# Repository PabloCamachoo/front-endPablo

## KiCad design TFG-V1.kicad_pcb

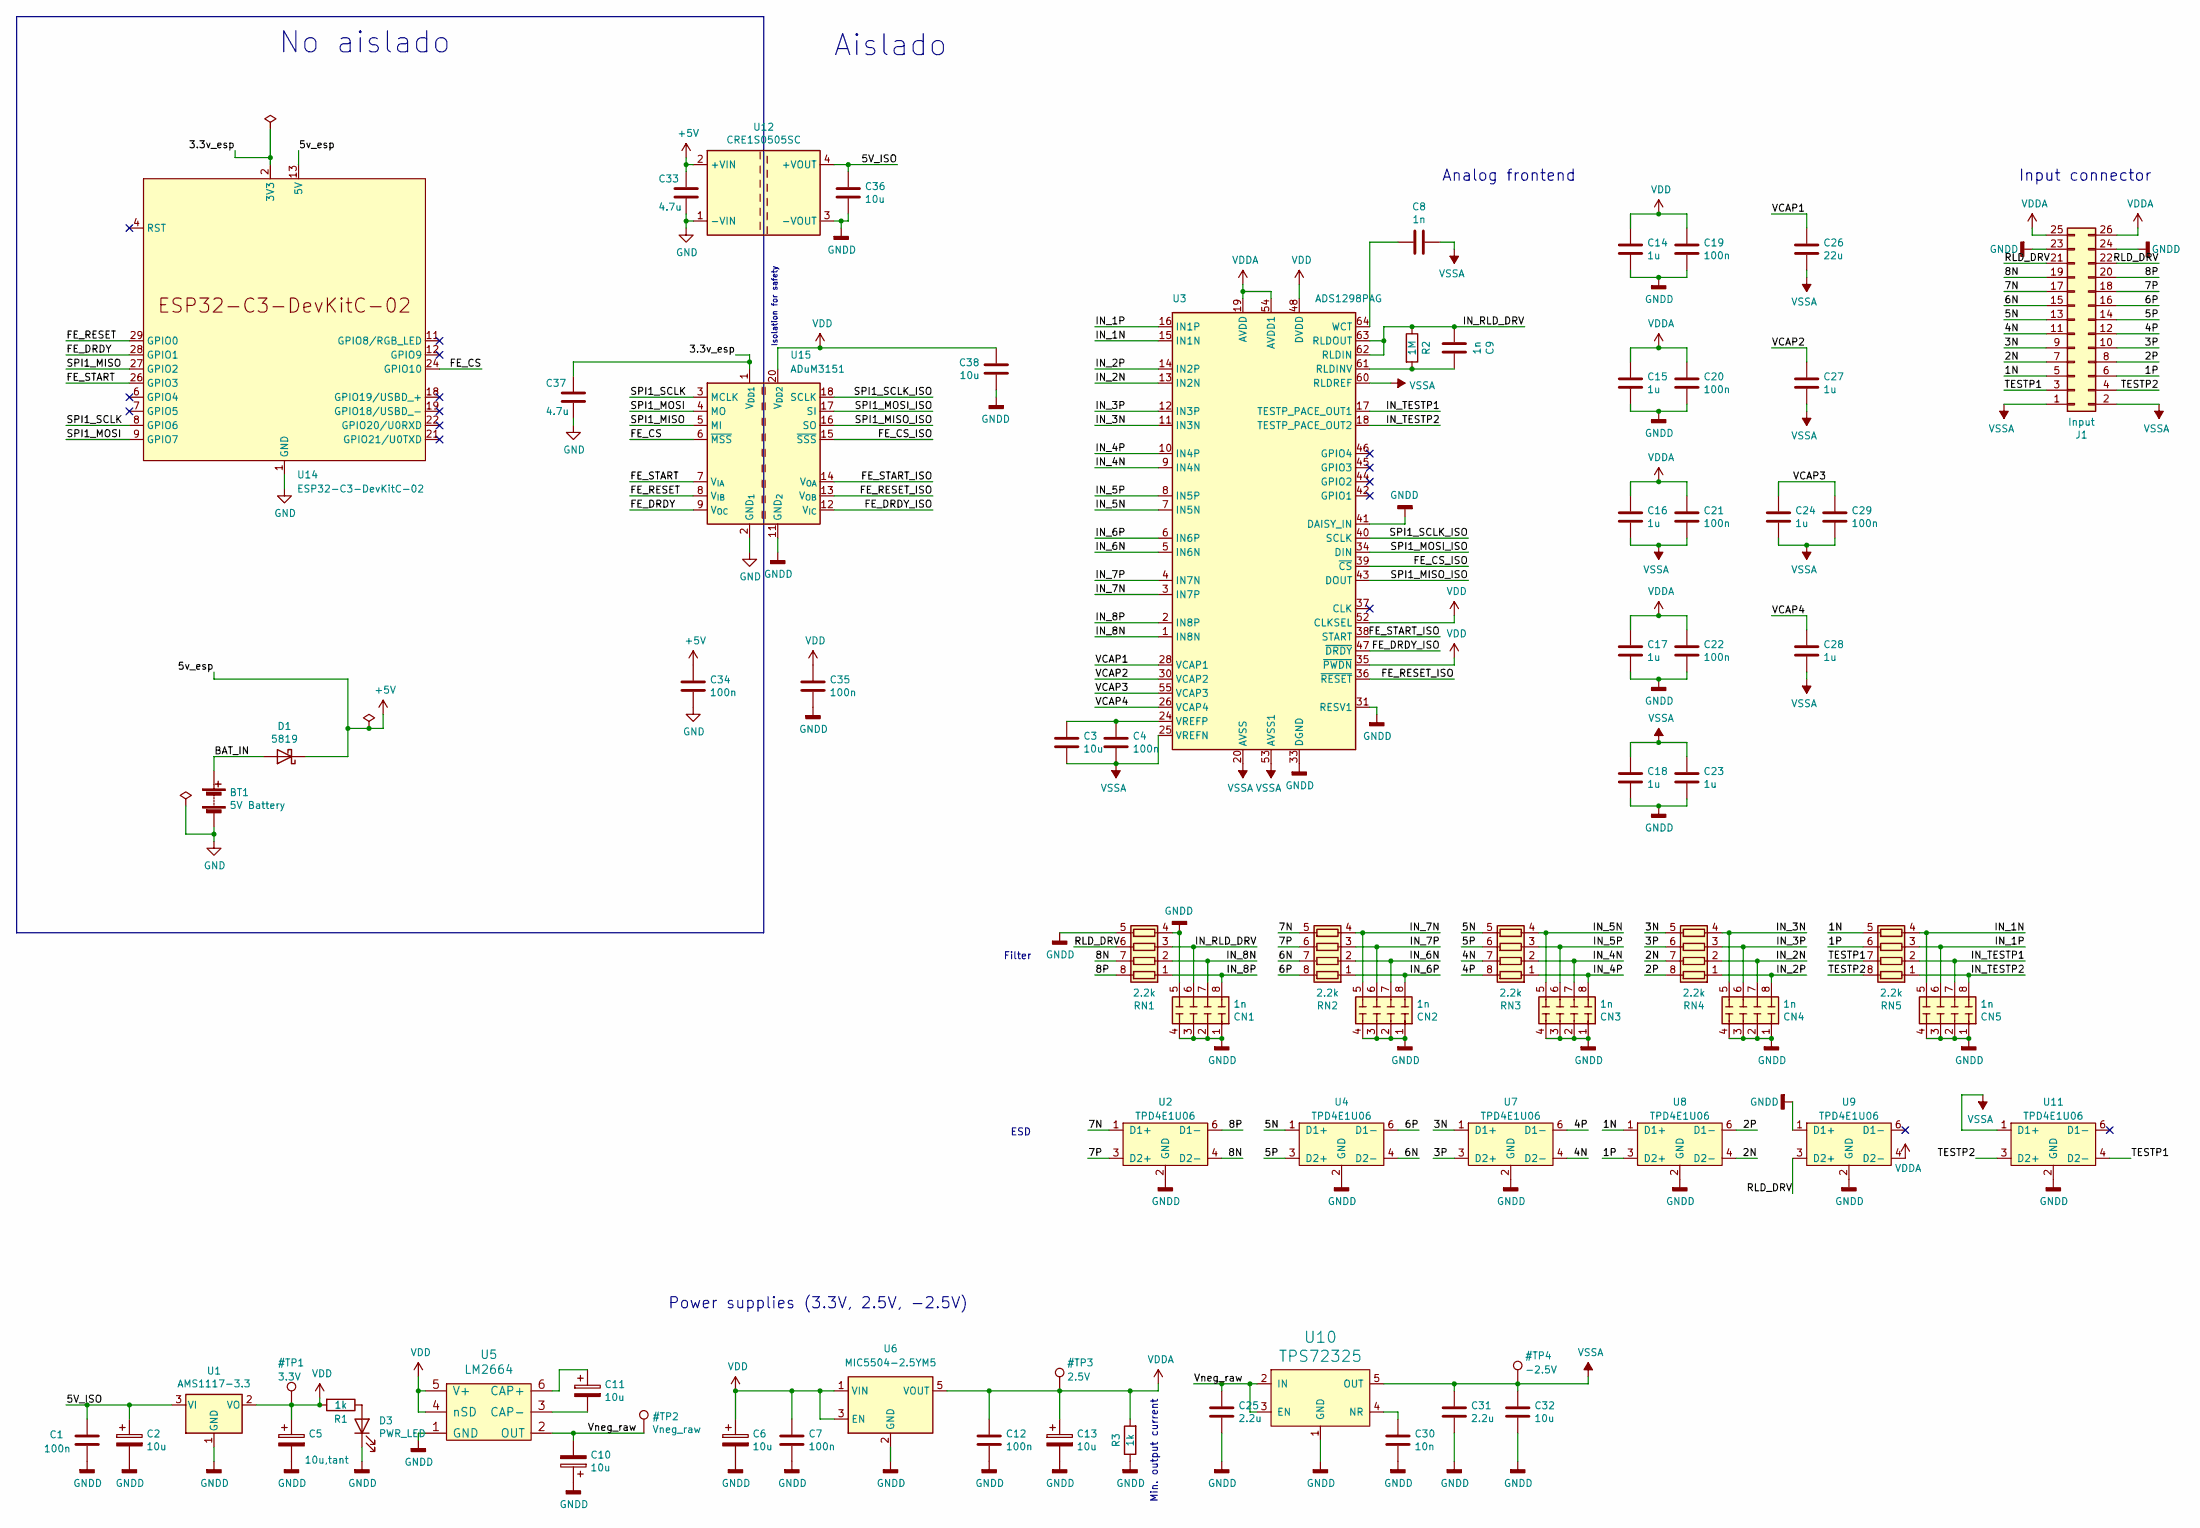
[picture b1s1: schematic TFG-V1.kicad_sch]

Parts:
BT1: 5V Battery; PinHeader_1x02_P2.54mm_Vertical
C1, C4, C7, C12, C19, C20, C21, C22, C29, C34, C35: 100n; C_0805_2012Metric_Pad1.18x1.45mm_HandSolder; LCSC C476766
C2, C3, C6, C10, C11, C13, C32, C36, C38: 10u; C_0805_2012Metric_Pad1.18x1.45mm_HandSolder; LCSC C40894
C5: 10u,tant; C_0805_2012Metric_Pad1.18x1.45mm_HandSolder; LCSC C110055
C8, C9: 1n; C_0805_2012Metric_Pad1.18x1.45mm_HandSolder; LCSC C277515
C14, C15, C16, C17, C18, C23, C24, C27, C28: 1u; C_0805_2012Metric_Pad1.18x1.45mm_HandSolder; LCSC C28323
C25, C31: 2.2u; C_0805_2012Metric_Pad1.18x1.45mm_HandSolder; LCSC C87994
C26: 22u; C_0805_2012Metric_Pad1.18x1.45mm_HandSolder; LCSC C129302
C30: 10n; C_0805_2012Metric_Pad1.18x1.45mm_HandSolder; LCSC C52278
C33, C37: 4.7u; C_0805_2012Metric_Pad1.18x1.45mm_HandSolder; LCSC C1779
CN1, CN2, CN3, CN4, CN5: 1n; R_Array_Convex_4x0603; LCSC C507409
D1: 5819; D_SOD-123; LCSC C82544
D3: PWR_LED; LED_0805_2012Metric; LCSC C72037
J1: Input; PinHeader_2x13_P2.54mm_Vertical; LCSC C358714
R1, R3: 1k; R_0805_2012Metric; LCSC C17513
R2: 1M; R_0805_2012Metric; LCSC C17514
RN1, RN2, RN3, RN4, RN5: 2.2k; R_Array_Convex_4x0603; LCSC C12001
U1: AMS1117-3.3; SOT-223-3_TabPin2; LCSC C6186
U2, U4, U7, U8, U9, U11: TPD4E1U06; SOT-23-6; LCSC C124691
U3: ADS1298PAG; TQFP-64_10x10mm_P0.5mm
U5: LM2664; SOT-23-6; LCSC C108573
U6: MIC5504-2.5YM5; SOT-23-5
U10: TPS72325; SOT-23-5; LCSC C69932
U12: CRE1S0505SC; Converter_DCDC_Murata_CRE1xxxxxxSC_THT; LCSC C18424
U14: ESP32-C3-DevKitC-02
U15: ADuM3151; SSOP-20_5.3x7.2mm_P0.65mm

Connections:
3V3: C37.1, U14.2 (3V3), U14.3 (3V3), U15.1 (V_{DD1})
+5V: C33.1, C34.1, D1.1 (K), U12.2 (+VIN), U14.13 (5V), U14.14 (5V)
/1N: J1.5, RN5.5 (R4.2), U8.1 (D1+)
/1P: J1.6, RN5.6 (R3.2), U8.3 (D2+)
/2N: J1.7, RN4.7 (R2.2), U8.4 (D2-)
/2P: J1.8, RN4.8 (R1.2), U8.6 (D1-)
/3N: J1.9, RN4.5 (R4.2), U7.1 (D1+)
/3P: J1.10, RN4.6 (R3.2), U7.3 (D2+)
/4N: J1.11, RN3.7 (R2.2), U7.4 (D2-)
/4P: J1.12, RN3.8 (R1.2), U7.6 (D1-)
/5N: J1.13, RN3.5 (R4.2), U4.1 (D1+)
/5P: J1.14, RN3.6 (R3.2), U4.3 (D2+)
/5V_ISO: C1.1, C2.1, C36.1, U1.3 (VI), U12.4 (+VOUT)
/6N: J1.15, RN2.7 (R2.2), U4.4 (D2-)
/6P: J1.16, RN2.8 (R1.2), U4.6 (D1-)
/7N: J1.17, RN2.5 (R4.2), U2.1 (D1+)
/7P: J1.18, RN2.6 (R3.2), U2.3 (D2+)
/8N: J1.19, RN1.7 (R2.2), U2.4 (D2-)
/8P: J1.20, RN1.8 (R1.2), U2.6 (D1-)
/BAT_IN: BT1.1 (+), D1.2 (A)
/FE_CS: U14.24 (GPIO10), U15.6 (~MSS)
/FE_CS_ISO: U3.39 (~CS), U15.15 (~SSS)
/FE_DRDY: U14.28 (GPIO1), U15.9 (V_{OC})
/FE_DRDY_ISO: U3.47 (~DRDY), U15.12 (V_{IC})
/FE_RESET: U14.29 (GPIO0), U15.8 (V_{IB})
/FE_RESET_ISO: U3.36 (~RESET), U15.13 (V_{OB})
/FE_START: U14.26 (GPIO3), U15.7 (V_{IA})
/FE_START_ISO: U3.38 (START), U15.14 (V_{OA})
/IN_1N: CN5.5 (R4.2), RN5.4 (R4.1), U3.15 (IN1N)
/IN_1P: CN5.6 (R3.2), RN5.3 (R3.1), U3.16 (IN1P)
/IN_2N: CN4.7 (R2.2), RN4.2 (R2.1), U3.13 (IN2N)
/IN_2P: CN4.8 (R1.2), RN4.1 (R1.1), U3.14 (IN2P)
/IN_3N: CN4.5 (R4.2), RN4.4 (R4.1), U3.11 (IN3N)
/IN_3P: CN4.6 (R3.2), RN4.3 (R3.1), U3.12 (IN3P)
/IN_4N: CN3.7 (R2.2), RN3.2 (R2.1), U3.9 (IN4N)
/IN_4P: CN3.8 (R1.2), RN3.1 (R1.1), U3.10 (IN4P)
/IN_5N: CN3.5 (R4.2), RN3.4 (R4.1), U3.7 (IN5N)
/IN_5P: CN3.6 (R3.2), RN3.3 (R3.1), U3.8 (IN5P)
/IN_6N: CN2.7 (R2.2), RN2.2 (R2.1), U3.5 (IN6N)
/IN_6P: CN2.8 (R1.2), RN2.1 (R1.1), U3.6 (IN6P)
/IN_7N: CN2.5 (R4.2), RN2.4 (R4.1), U3.3 (IN7P)
/IN_7P: CN2.6 (R3.2), RN2.3 (R3.1), U3.4 (IN7N)
/IN_8N: CN1.7 (R2.2), RN1.2 (R2.1), U3.1 (IN8N)
/IN_8P: CN1.8 (R1.2), RN1.1 (R1.1), U3.2 (IN8P)
/IN_RLD_DRV: C9.2, CN1.6 (R3.2), R2.1, RN1.3 (R3.1), U3.62 (RLDIN), U3.63 (RLDOUT)
/IN_TESTP1: CN5.7 (R2.2), RN5.2 (R2.1), U3.17 (TESTP_PACE_OUT1)
/IN_TESTP2: CN5.8 (R1.2), RN5.1 (R1.1), U3.18 (TESTP_PACE_OUT2)
/RLD_DRV: J1.21, J1.22, RN1.6 (R3.2), U9.3 (D2+)
/SPI1_MISO: U14.27 (GPIO2), U15.5 (MI)
/SPI1_MISO_ISO: U3.43 (DOUT), U15.16 (SO)
/SPI1_MOSI: U14.9 (GPIO7), U15.4 (MO)
/SPI1_MOSI_ISO: U3.34 (DIN), U15.17 (SI)
/SPI1_SCLK: U14.8 (GPIO6), U15.3 (MCLK)
/SPI1_SCLK_ISO: U3.40 (SCLK), U15.18 (SCLK)
/TESTP1: J1.3, RN5.7 (R2.2), U11.4 (D2-)
/TESTP2: J1.4, RN5.8 (R1.2), U11.3 (D2+)
/VCAP1: C26.1, U3.28 (VCAP1)
/VCAP2: C27.1, U3.30 (VCAP2)
/VCAP3: C24.1, C29.1, U3.55 (VCAP3)
/VCAP4: C28.1, U3.26 (VCAP4)
/Vneg_raw: C10.2, C25.1, U5.2 (OUT), U10.2 (IN), U10.3 (EN)
GND: BT1.2 (-), C33.2, C34.2, C37.2, U12.1 (-VIN), U14.1 (GND), U14.5 (GND), U14.10 (GND), U14.15 (GND), U14.16 (GND), U14.17 (GND), U14.20 (GND), U14.23 (GND), U14.25 (GND), U14.30 (GND), U15.2 (GND_{1}), U15.10 (GND_{1})
GNDD: C1.2, C2.2, C5.2, C6.2, C7.2, C10.1, C12.2, C13.2, C14.2, C15.2, C17.2, C18.2, C19.2, C20.2, C22.2, C23.2, C25.2, C30.2, C31.2, C32.2, C35.2, C36.2, C38.2, CN1.1 (R1.1), CN1.2 (R2.1), CN1.3 (R3.1), CN1.4 (R4.1), CN1.5 (R4.2), CN2.1 (R1.1), CN2.2 (R2.1), CN2.3 (R3.1), CN2.4 (R4.1), CN3.1 (R1.1), CN3.2 (R2.1), CN3.3 (R3.1), CN3.4 (R4.1), CN4.1 (R1.1), CN4.2 (R2.1), CN4.3 (R3.1), CN4.4 (R4.1), CN5.1 (R1.1), CN5.2 (R2.1), CN5.3 (R3.1), CN5.4 (R4.1), D3.1 (K), J1.23, J1.24, R3.1, RN1.4 (R4.1), RN1.5 (R4.2), U1.1 (GND), U2.2 (GND), U3.31 (RESV1), U3.33 (DGND), U3.41 (DAISY_IN), U3.49 (DGND), U3.51 (DGND), U4.2 (GND), U5.1 (GND), U6.2 (GND), U7.2 (GND), U8.2 (GND), U9.1 (D1+), U9.2 (GND), U10.1 (GND), U11.2 (GND), U12.3 (-VOUT), U15.11 (GND_{2}), U15.19 (GND_{2})
unnamed: D3.2 (A), R1.1
unnamed: C9.1, R2.2, U3.61 (RLDINV)
unnamed: C3.1, C4.1, U3.24 (VREFP)
unnamed: C8.2, U3.64 (WCT)
unnamed: C11.1, U5.6 (CAP+)
unnamed: C11.2, U5.3 (CAP-)
unnamed: C30.1, U10.4 (NR)
VDD: C5.1, C6.1, C7.1, C14.1, C19.1, C35.1, C38.1, R1.2, U1.2 (VO), U3.35 (~PWDN), U3.48 (DVDD), U3.50 (DVDD), U3.52 (CLKSEL), U5.4 (nSD), U5.5 (V+), U6.1 (VIN), U6.3 (EN), U15.20 (V_{DD2})
VDDA: C12.1, C13.1, C15.1, C16.1, C17.1, C20.1, C21.1, C22.1, J1.25, J1.26, R3.2, U3.19 (AVDD), U3.21 (AVDD), U3.22 (AVDD), U3.54 (AVDD1), U3.56 (AVDD), U3.59 (AVDD), U6.5 (VOUT), U9.4 (D2-)
VSSA: C3.2, C4.2, C8.1, C16.2, C18.1, C21.2, C23.1, C24.2, C26.2, C27.2, C28.2, C29.2, C31.1, C32.1, J1.1, J1.2, U3.20 (AVSS), U3.23 (AVSS), U3.25 (VREFN), U3.32 (AVSS), U3.53 (AVSS1), U3.57 (AVSS), U3.58 (AVSS), U3.60 (RLDREF), U10.5 (OUT), U11.1 (D1+)

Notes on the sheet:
Analog frontend
Aislado
Input connector
Isolation for safety
Min. output current
Filter
Power supplies (3.3V, 2.5V, -2.5V)
ESD
No aislado

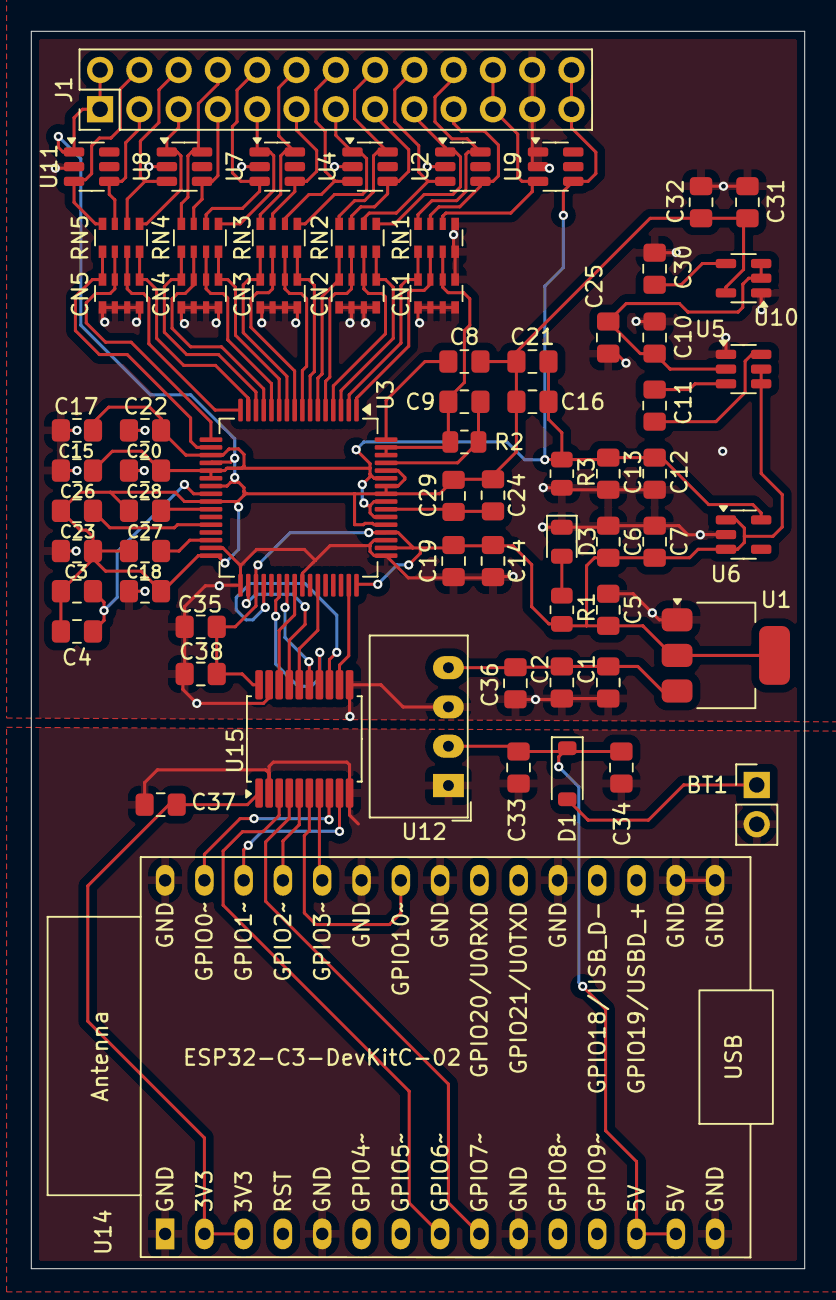
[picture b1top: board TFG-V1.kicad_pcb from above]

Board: 2 copper layers, 50.0 x 80.0 mm, 69 parts (0 on the bottom side), 73 nets.

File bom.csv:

"Reference","Value","Footprint","Qty","DNP"
"BT1","6V Battery","Connector_JST:JST_XH_S2B-XH-A-1_1x02_P2.50mm_Horizontal","1",""
"C1,C4,C7,C12,C19,C20,C21,C22,C29,C34,C35","100n","Capacitor_SMD:C_0805_2012Metric","11",""
"C2,C3,C6,C10,C11,C13,C32,C36","10u","Capacitor_SMD:C_0805_2012Metric","8",""
"C5","10u,tant","Capacitor_Tantalum_SMD:CP_EIA-3216-10_Kemet-I","1",""
"C8,C9,CN1,CN2,CN3,CN4,CN5","1n","-- valores mixtos --","7",""
"C14,C15,C16,C17,C18,C23,C24,C27,C28","1u","Capacitor_SMD:C_0805_2012Metric","9",""
"C25,C31","2.2u","Capacitor_SMD:C_0805_2012Metric","2",""
"C26","22u","Capacitor_SMD:C_0805_2012Metric","1",""
"C30","10n","Capacitor_SMD:C_0805_2012Metric","1",""
"C33","4.7u","Capacitor_SMD:C_0805_2012Metric","1",""
"D1,D2","5819","Diode_SMD:D_SOD-123","2",""
"D3","PWR_LED","LED_SMD:LED_0805_2012Metric","1",""
"J1","Input","Connector_PinHeader_2.54mm:PinHeader_2x13_P2.54mm_Horizontal","1",""
"R1,R3","1k","Resistor_SMD:R_0805_2012Metric","2",""
"R2","1M","Resistor_SMD:R_0805_2012Metric","1",""
"RN1,RN2,RN3,RN4,RN5","2.2k","Resistor_SMD:R_Array_Convex_4x0603","5",""
"U1","AMS1117-3.3","Package_TO_SOT_SMD:SOT-223-3_TabPin2","1",""
"U2,U4,U7,U8,U9,U11","TPD4E1U06","Package_TO_SOT_SMD:SOT-23-6","6",""
"U3","ADS1298PAG","Package_QFP:TQFP-64_10x10mm_P0.5mm","1",""
"U5","LM2664","Package_TO_SOT_SMD:SOT-23-6","1",""
"U6","HT7525-7","Package_TO_SOT_SMD:SOT-23-5","1",""
"U10","TPS72325","Package_TO_SOT_SMD:SOT-23-5","1",""
"U12","CRE1S0505SC","Converter_DCDC:Converter_DCDC_Murata_CRE1xxxxxxSC_THT","1",""
"U14","ESP32-C3-DevKitC-02","PCM_Espressif:ESP32-C3-DevKitC-02","1",""
"U15","ADuM3151","Package_SO:SSOP-20_5.3x7.2mm_P0.65mm","1",""

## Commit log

2025-01-07 arreglo1
2025-01-10 correcciones varias 1
    reruteo y corregir algunas cosas
2025-01-17 diseño final
2026-03-17 gitignore bakcups
